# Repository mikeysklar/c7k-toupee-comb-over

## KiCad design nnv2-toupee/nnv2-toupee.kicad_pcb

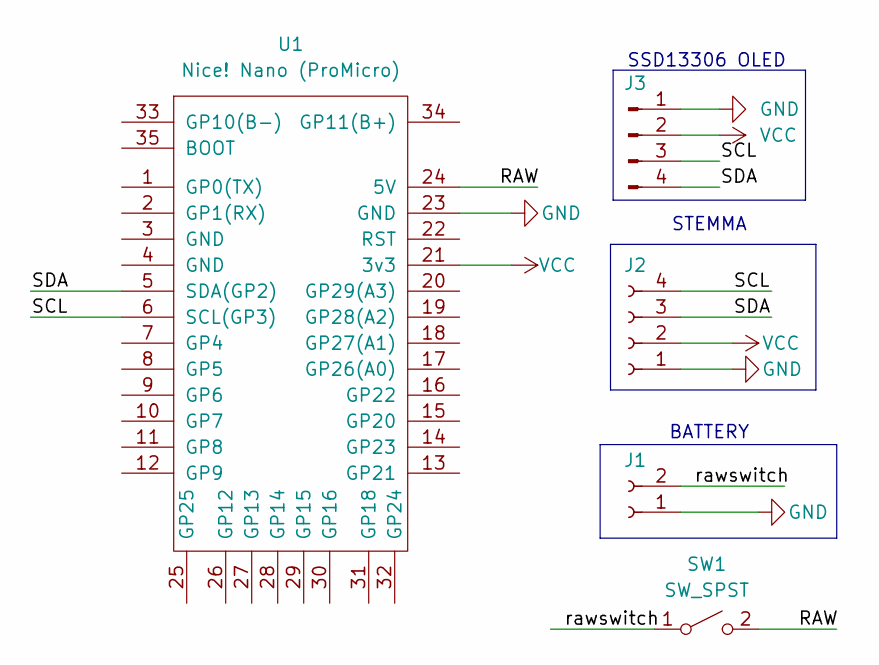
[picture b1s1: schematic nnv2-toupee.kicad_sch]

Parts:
J1: Conn_01x02_Socket; JST_PH_S2B-PH-SM4-TB_1x02-1MP_P2.00mm_Horizontal
J2: Conn_01x04_Socket; JST_SH4
J3: Conn_01x04_Pin; ssd1306-toupee
SW1: SW_SPST; Untitled
U1: Nice! Nano (ProMicro); SuperMini NRF52840

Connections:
/RAW: SW1.2 (B), U1.24 (5V)
/SCL: J2.4, J3.3, U1.6 (SCL(GP3))
/SDA: J2.3, J3.4, U1.5 (SDA(GP2))
/rawswitch: J1.2, SW1.1 (A)
GND: J1.1, J2.1, J3.1, U1.23 (GND)
VCC: J2.2, J3.2, U1.21 (3v3)

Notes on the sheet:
STEMMA
BATTERY
SSD13306 OLED

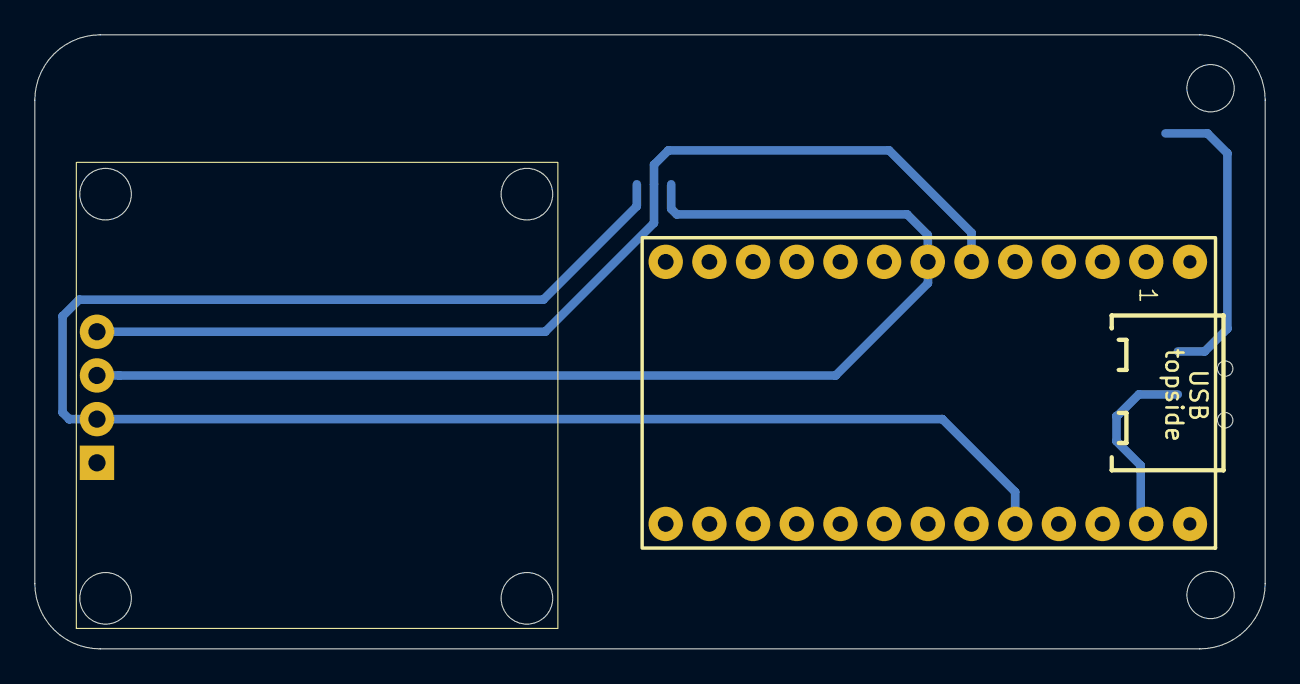
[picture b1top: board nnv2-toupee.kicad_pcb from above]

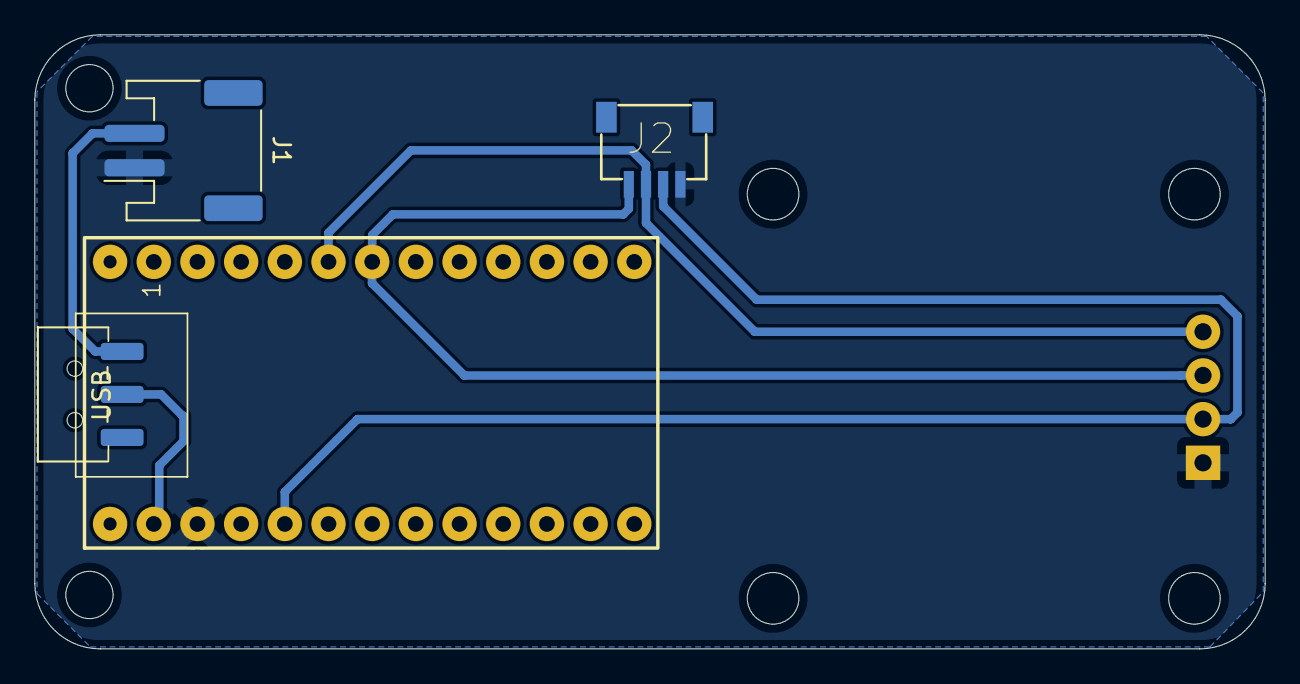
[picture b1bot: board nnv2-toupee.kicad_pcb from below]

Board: 2 copper layers, 71.5 x 35.7 mm, 5 parts (3 on the bottom side), 6 nets.

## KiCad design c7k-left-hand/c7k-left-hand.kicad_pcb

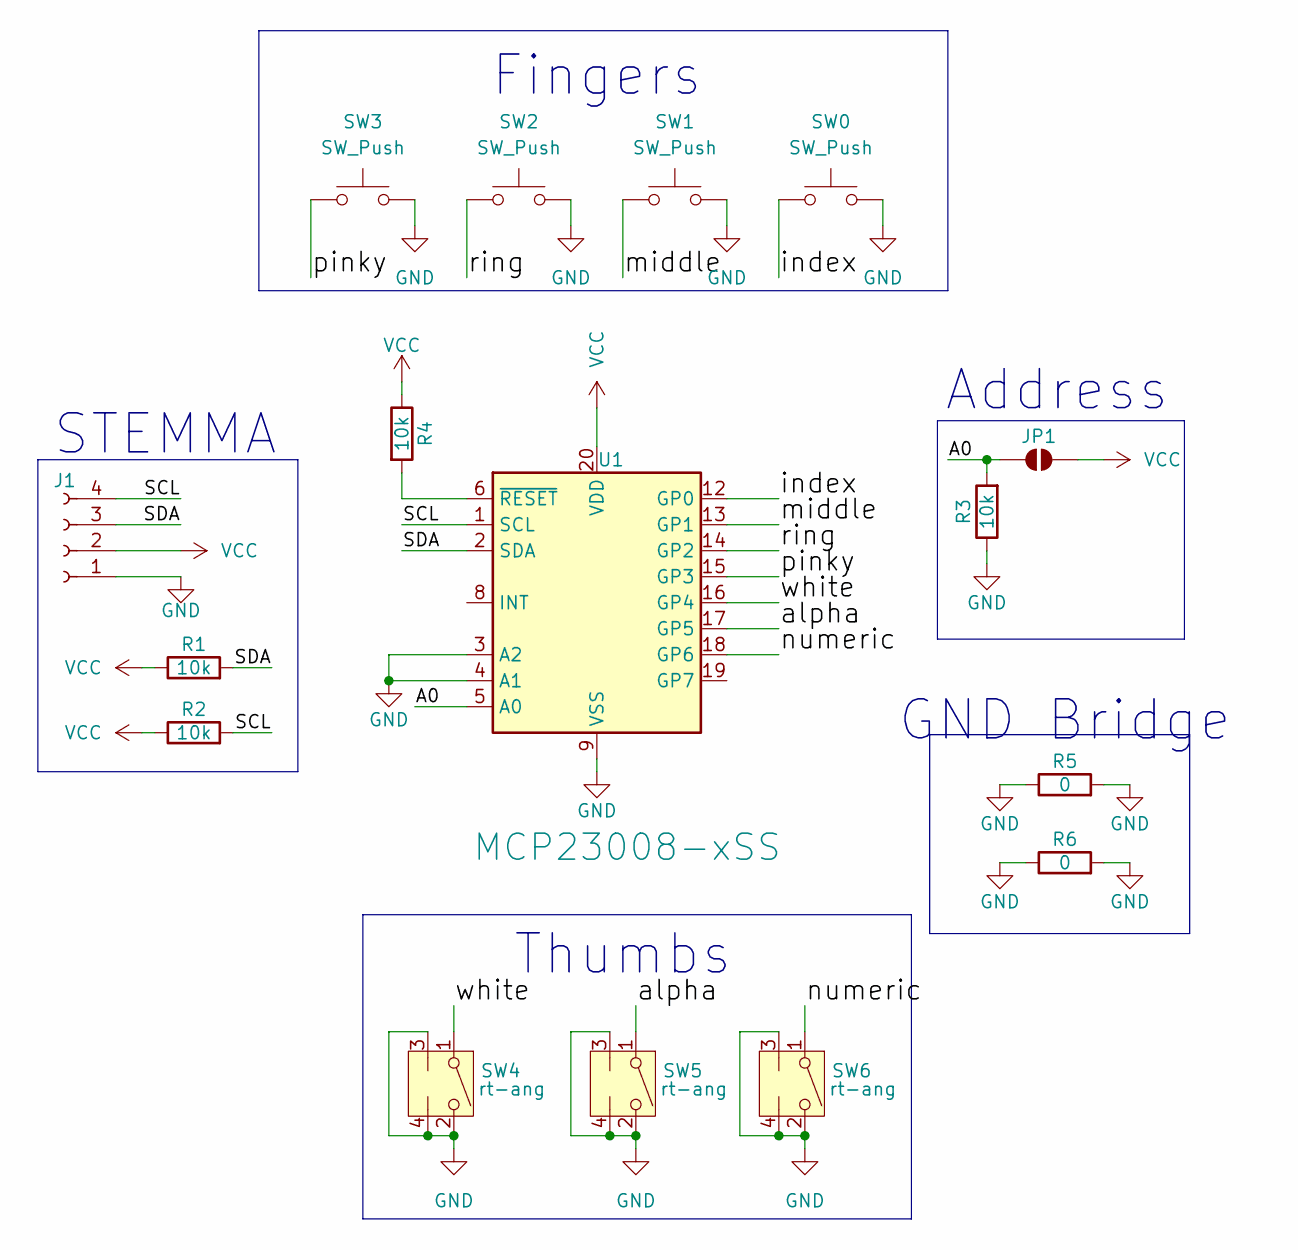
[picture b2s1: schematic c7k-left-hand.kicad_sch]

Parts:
J1: Conn_01x04_Socket; JST_SH_SM04B-SRSS-TB_1x04-1MP_P1.00mm_Horizontal
JP1: SolderJumper_2_Open; SolderJumper-2_P1.3mm_Open_TrianglePad1.0x1.5mm
R1, R2, R3, R4: 10k; R_0805_2012Metric_Pad1.20x1.40mm_HandSolder
R5, R6: 0; R_0805_2012Metric_Pad1.20x1.40mm_HandSolder
SW0, SW1, SW2, SW3: SW_Push; Kailh_socket_PG1350
SW4, SW5, SW6: rt-ang; SW_Tactile_SPST_Angled_PTS645Vx83-2LFS
U1: MCP23008-xSS; SSOP-20_5.3x7.2mm_P0.65mm

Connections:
/A0: JP1.1 (A), R3.2, U1.5 (A0)
/SCL: J1.4, R2.2, U1.1 (SCL)
/SDA: J1.3, R1.2, U1.2 (SDA)
/alpha: SW5.1, U1.17 (GP5)
/index: SW0.1, U1.12 (GP0)
/middle: SW1.1, U1.13 (GP1)
/numeric: SW6.1, U1.18 (GP6)
/pinky: SW3.1, U1.15 (GP3)
/ring: SW2.1, U1.14 (GP2)
/white: SW4.1, U1.16 (GP4)
GND: J1.1, R3.1, R5.1, R5.2, R6.1, R6.2, SW0.2, SW1.2, SW2.2, SW3.2, SW4.2, SW4.3 (L), SW4.4 (L), SW5.2, SW5.3 (L), SW5.4 (L), SW6.2, SW6.3 (L), SW6.4 (L), U1.3 (A2), U1.4 (A1), U1.9 (VSS)
unnamed: R4.2, U1.6 (~RESET)
VCC: J1.2, JP1.2 (B), R1.1, R2.1, R4.1, U1.20 (VDD)

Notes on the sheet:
GND Bridge
Fingers
Thumbs
Address
STEMMA

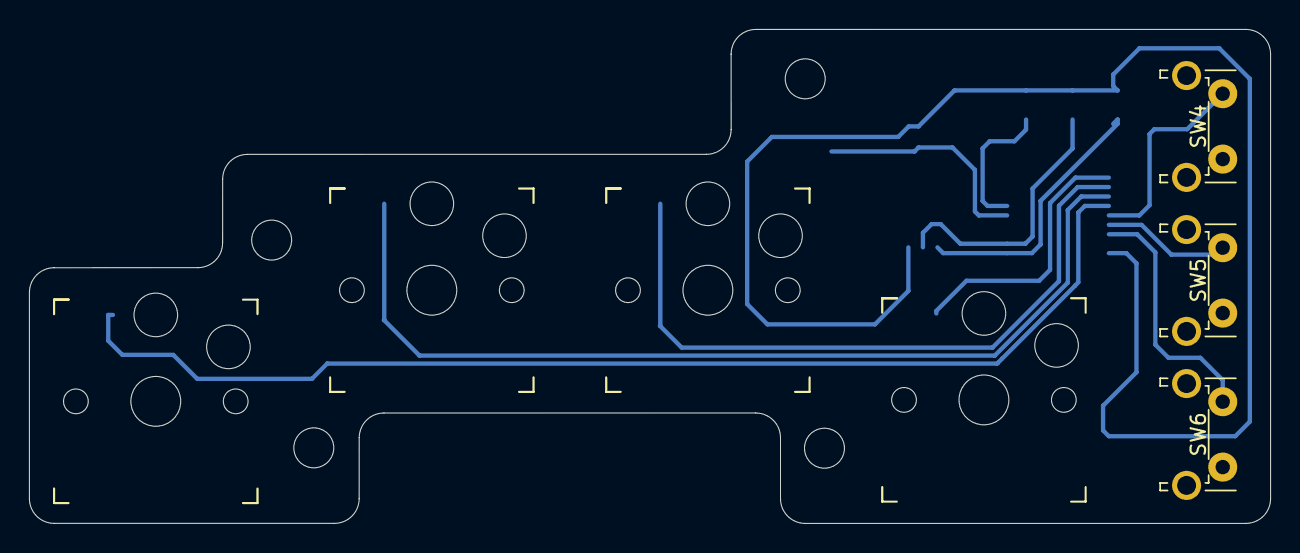
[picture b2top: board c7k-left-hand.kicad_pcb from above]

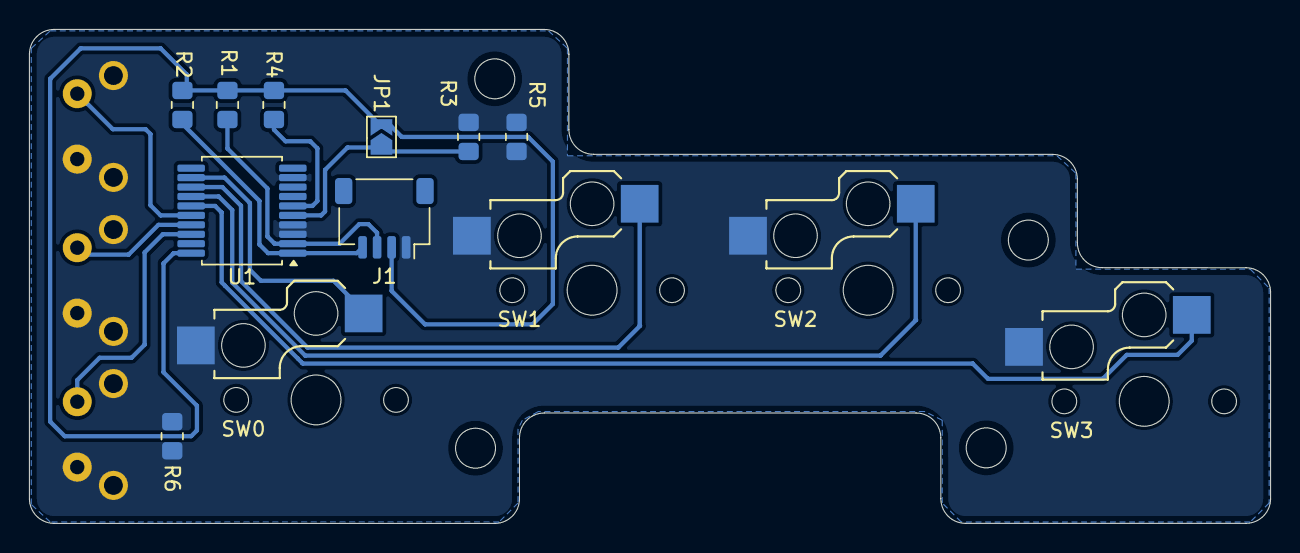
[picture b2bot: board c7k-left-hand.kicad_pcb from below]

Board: 2 copper layers, 85.4 x 34.0 mm, 16 parts (9 on the bottom side), 13 nets.

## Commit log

2025-05-09 init commit
2025-05-11 working towards a comb over
2025-05-13 case hinge
2025-05-14 adding source code
2025-05-14 updating design files
2025-05-17 walk away
2025-05-17 minor changes for board reprint
